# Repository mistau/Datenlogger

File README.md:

# Datenlogger
Flexible data logger working for many months on cheap AA batteries.

## Status
PCB back from fab, populated and tested. Extensive testroutines available in folder hwtest.
Unfortunatelly PCB rev 1.0 has two missing connections (i2c bus) which requires two ugly wires.
This is fixed in HW revision 1.1.

## what's next
Application software for light sensor under development.

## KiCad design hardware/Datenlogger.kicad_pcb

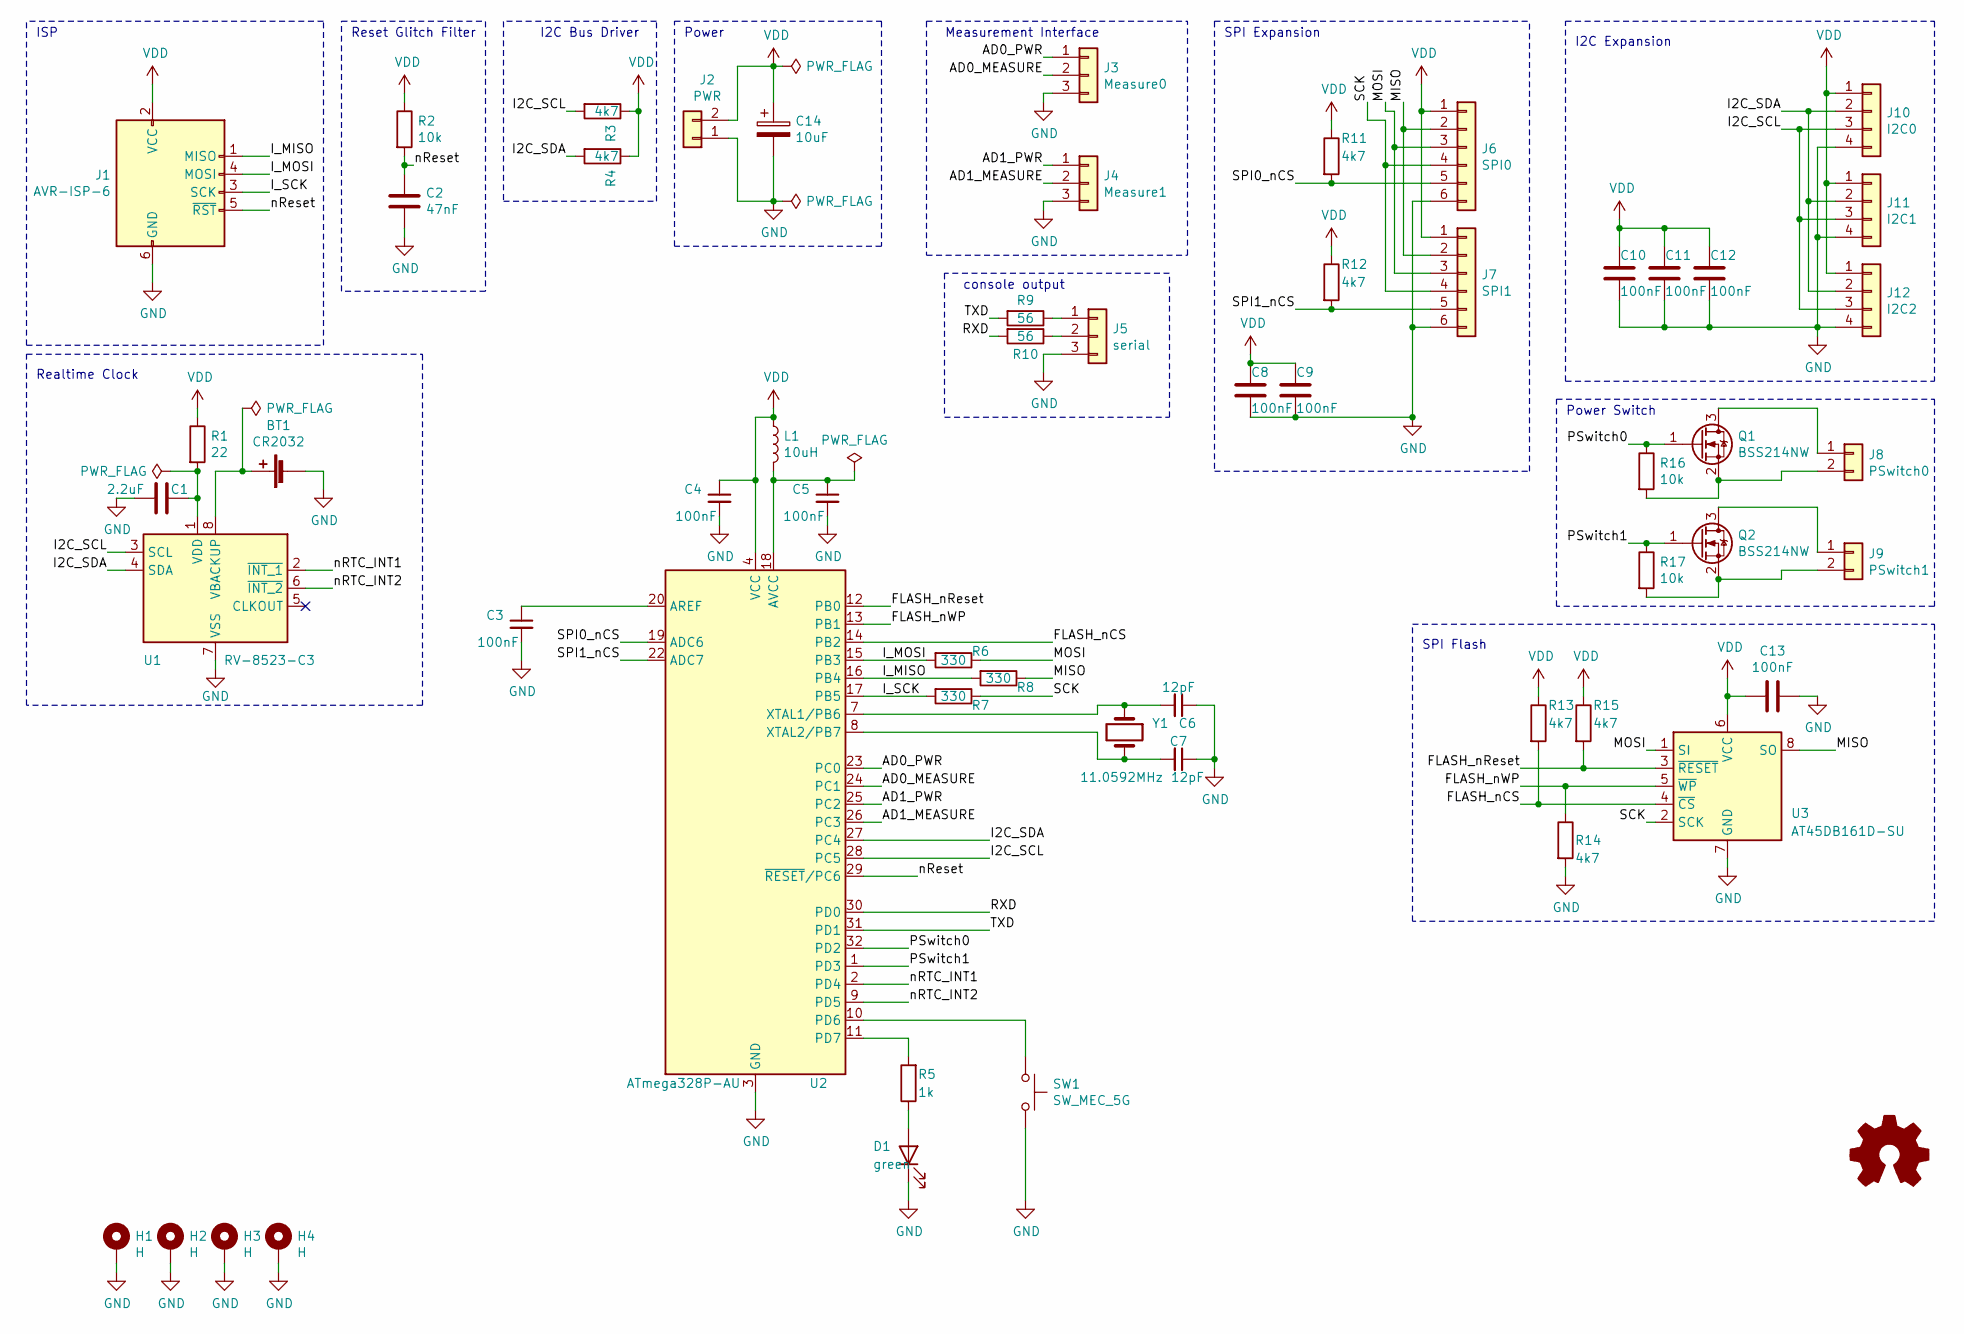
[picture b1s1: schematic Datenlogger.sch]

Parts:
BT1: CR2032; Battery_Panasonic_CR2032-VS1N_Vertical_CircularHoles
C1: 2.2uF; C_0603_1608Metric_Pad1.08x0.95mm_HandSolder
C2: 47nF; C_0603_1608Metric_Pad1.08x0.95mm_HandSolder
C3, C4, C5, C8, C9, C10, C11, C12, C13: 100nF; C_0603_1608Metric_Pad1.08x0.95mm_HandSolder
C6, C7: 12pF; C_0603_1608Metric_Pad1.08x0.95mm_HandSolder
C14: 10uF; CP_Elec_4x5.4
D1: green; D_0603_1608Metric_Pad1.05x0.95mm_HandSolder
H1, H2, H3, H4: H; MountingHole_3.2mm_M3_Pad_TopBottom
J1: AVR-ISP-6; PinHeader_2x03_P2.54mm_Vertical
J2: PWR; Molex_SPOX_5267-02A_1x02_P2.50mm_Vertical
J3: Measure0; Molex_KK-254_AE-6410-03A_1x03_P2.54mm_Vertical
J4: Measure1; Molex_KK-254_AE-6410-03A_1x03_P2.54mm_Vertical
J5: serial; PinHeader_1x03_P2.54mm_Vertical
J6: SPI0; Molex_KK-254_AE-6410-06A_1x06_P2.54mm_Vertical
J7: SPI1; Molex_KK-254_AE-6410-06A_1x06_P2.54mm_Vertical
J8: PSwitch0; Molex_KK-254_AE-6410-02A_1x02_P2.54mm_Vertical
J9: PSwitch1; Molex_KK-254_AE-6410-02A_1x02_P2.54mm_Vertical
J10: I2C0; Molex_KK-254_AE-6410-04A_1x04_P2.54mm_Vertical
J11: I2C1; Molex_KK-254_AE-6410-04A_1x04_P2.54mm_Vertical
J12: I2C2; Molex_KK-254_AE-6410-04A_1x04_P2.54mm_Vertical
L1: 10uH; L_0603_1608Metric_Pad1.05x0.95mm_HandSolder
Q1, Q2: BSS214NW; SOT-323_SC-70
R1: 22; R_0603_1608Metric_Pad0.98x0.95mm_HandSolder
R2, R16, R17: 10k; R_0603_1608Metric_Pad0.98x0.95mm_HandSolder
R3, R4, R11, R12, R13, R14, R15: 4k7; R_0603_1608Metric_Pad0.98x0.95mm_HandSolder
R5: 1k; R_0603_1608Metric_Pad0.98x0.95mm_HandSolder
R6, R7, R8: 330; R_0603_1608Metric_Pad0.98x0.95mm_HandSolder
R9, R10: 56; R_0603_1608Metric_Pad0.98x0.95mm_HandSolder
SW1: SW_MEC_5G; SW_SPST_Omron_B3FS-100xP
U1: RV-8523-C3; RTC_SMD_MicroCrystal_C3_2.5x3.7mm
U2: ATmega328P-AU; TQFP-32_7x7mm_P0.8mm
U3: AT45DB161D-SU; SOIC-8_5.275x5.275mm_P1.27mm
Y1: 11.0592MHz; Crystal_SMD_HC49-SD

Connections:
/AD0_MEASURE: J3.2, U2.24 (PC1)
/AD0_PWR: J3.1, U2.23 (PC0)
/AD1_MEASURE: J4.2, U2.26 (PC3)
/AD1_PWR: J4.1, U2.25 (PC2)
/FLASH_nCS: R13.2, U2.14 (PB2), U3.4 (~CS)
/FLASH_nReset: R15.2, U2.12 (PB0), U3.3 (~RESET~)
/FLASH_nWP: R14.1, U2.13 (PB1), U3.5 (~WP)
/I2C_SCL: J10.3, J11.3, J12.3, R3.2, U1.3 (SCL), U2.28 (PC5)
/I2C_SDA: J10.2, J11.2, J12.2, R4.2, U1.4 (SDA), U2.27 (PC4)
/I_MISO: J1.1 (MISO), R8.2, U2.16 (PB4)
/I_MOSI: J1.4 (MOSI), R6.2, U2.15 (PB3)
/I_SCK: J1.3 (SCK), R7.2, U2.17 (PB5)
/MISO: J6.2, J7.2, R8.1, U3.8 (SO)
/MOSI: J6.3, J7.3, R6.1, U3.1 (SI)
/PSwitch0: Q1.1 (G), R16.1, U2.32 (PD2)
/PSwitch1: Q2.1 (G), R17.1, U2.1 (PD3)
/RXD: R10.2, U2.30 (PD0)
/SCK: J6.4, J7.4, R7.1, U3.2 (SCK)
/SPI0_nCS: J6.5, R11.2, U2.19 (ADC6)
/SPI1_nCS: J7.5, R12.2, U2.22 (ADC7)
/TXD: R9.2, U2.31 (PD1)
/nRTC_INT1: U1.2 (~INT_1), U2.2 (PD4)
/nRTC_INT2: U1.6 (~INT_2), U2.9 (PD5)
/nReset: C2.1, J1.5 (~RST), R2.2, U2.29 (~RESET~/PC6)
GND: BT1.2 (-), C1.2, C2.2, C3.2, C4.2, C5.2, C6.1, C7.1, C8.2, C9.2, C10.2, C11.2, C12.2, C13.1, C14.2, D1.1 (K), H1.1, H2.1, H3.1, H4.1, J1.6 (GND), J2.1, J3.3, J4.3, J5.3, J6.6, J7.6, J10.4, J11.4, J12.4, R14.2, SW1.3 (B), SW1.4 (B), U1.7 (VSS), U2.3 (GND), U2.5 (GND), U2.21 (GND), U3.7 (GND)
unnamed: BT1.1 (+), U1.8 (VBACKUP)
unnamed: C1.1, R1.2, U1.1 (VDD)
unnamed: C3.1, U2.20 (AREF)
unnamed: C5.1, L1.2, U2.18 (AVCC)
unnamed: C6.2, U2.7 (XTAL1/PB6), Y1.1
unnamed: C7.2, U2.8 (XTAL2/PB7), Y1.2
unnamed: D1.2 (A), R5.1
unnamed: J5.1, R9.1
unnamed: J5.2, R10.1
unnamed: J8.1, Q1.3 (D)
unnamed: J8.2, Q1.2 (S), R16.2
unnamed: J9.1, Q2.3 (D)
unnamed: J9.2, Q2.2 (S), R17.2
unnamed: R5.2, U2.11 (PD7)
unnamed: SW1.1 (A), SW1.2 (A), U2.10 (PD6)
VDD: C4.1, C8.1, C9.1, C10.1, C11.1, C12.1, C13.2, C14.1, J1.2 (VCC), J2.2, J6.1, J7.1, J10.1, J11.1, J12.1, L1.1, R1.1, R2.1, R3.1, R4.1, R11.1, R12.1, R13.1, R15.1, U2.4 (VCC), U2.6 (VCC), U3.6 (VCC)

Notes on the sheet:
I2C Bus Driver
ISP
Reset Glitch Filter
Realtime Clock
I2C Expansion
SPI Flash
Power Switch
SPI Expansion
Power
Measurement Interface
console output

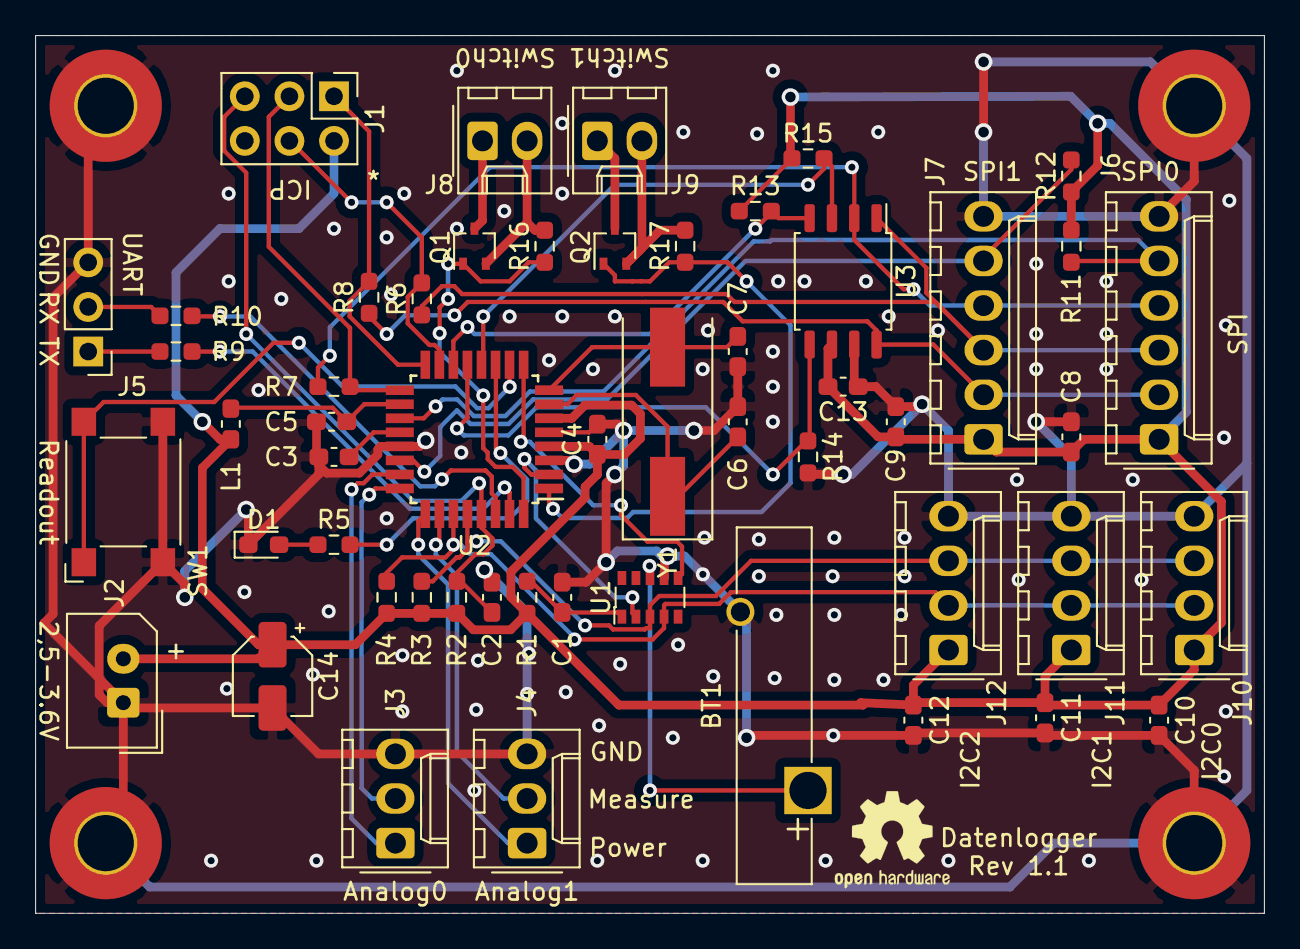
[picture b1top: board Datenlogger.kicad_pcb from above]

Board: 2 copper layers, 70.0 x 50.0 mm, 57 parts (0 on the bottom side), 41 nets.

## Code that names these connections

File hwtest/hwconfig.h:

/*
 * -------------------------------------------------------------------------
 * Controller fuer den Tauben Datenlogger
 * Version 0.1 fuer HW Rev 1.0
 * hardware definitionen
 * -------------------------------------------------------------------------
 *  M.Staudenmaier
 */

#ifndef _HWCONFIG_H_
#define _HWCONFIG_H_

/* the LEDs connections */
#define LED_STATE        PD7       /**< on-pcb status LED */

/* Input Keys */
#define BUTTON           PD6

/* Interrupt Inputs */
#define RTCINT1          PD4
#define RTCINT2          PD5

/* outputs */
#define PSWITCH0         PD2
#define PSWITCH1         PD3

/* connections to flash device */
#define FLASH_DDR    DDRB
#define FLASH_NRESET PB0
#define FLASH_NWP    PB1
#define FLASH_NCS    PB2

#endif

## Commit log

2021-01-26 initial hardware done.
2021-01-29 Updated oscilator to be suited for standard UART baudrates.
2021-02-12 fix: Minor fixes to the hardware
    Corrected text on allowed voltages to 2.6V-3.6V caused by the limits of the flash device.
    Modified value of R1 to 56Ohm as the original was clearly way too high.
    fixes #1
    fixes #2
2021-04-07 Fundamental HW Fix, added testsuite
    * fix #3 missing I2C connections
    * fix #4 different components for R1/C1 to ensure switch-over to battery
    * add extensive testsuite hwtest used to verify the HW.
2021-04-08 Cleaned up flash device test
    All test routines are enabled now to allow a test
    of the key board functionality.
2021-04-08 Enable battery in RTC.
